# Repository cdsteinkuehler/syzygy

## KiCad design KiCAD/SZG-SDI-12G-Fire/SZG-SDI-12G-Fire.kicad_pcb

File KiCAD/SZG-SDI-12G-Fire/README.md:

# SYZYGY 12G SDI Pod

This directory contains KiCad 7 design files for a SYZYGY 12G SDI Pod
intended to be used with the BeagleV-Fire SYZYGY connector and 12G
capable transceivers.

Near as I can tell, the SYZYGY Template PCB designs from Opal Kelly are
licensed under the SYZYGY Specification License Agreement (or at least
I was unable to find any other license information specifically related
to the PCB templates).  My changes to the template design are licensed
under the CERN CERN-OHL-P v2 (permissive) license to the extent this
does not conflict with the SYZYGY license agreement.

NOTE: Power rail separation for the SDI chips matches the Semtech Intel
FPGA Arria 10 Reference Design Daughter Card implementation vs. the
application circuit notes provided in the data sheets.

## License Info

Copyright Charles Steinkuehler 2024.

This source describes Open Hardware and is licensed under the CERN-OHL-P
v2

You may redistribute and modify this documentation and make products
using it under the terms of the CERN-OHL-P v2 (https:/cern.ch/cern-ohl).
This documentation is distributed WITHOUT ANY EXPRESS OR IMPLIED
WARRANTY, INCLUDING OF MERCHANTABILITY, SATISFACTORY QUALITY
AND FITNESS FOR A PARTICULAR PURPOSE. Please see the CERN-OHL-P v2
for applicable conditions

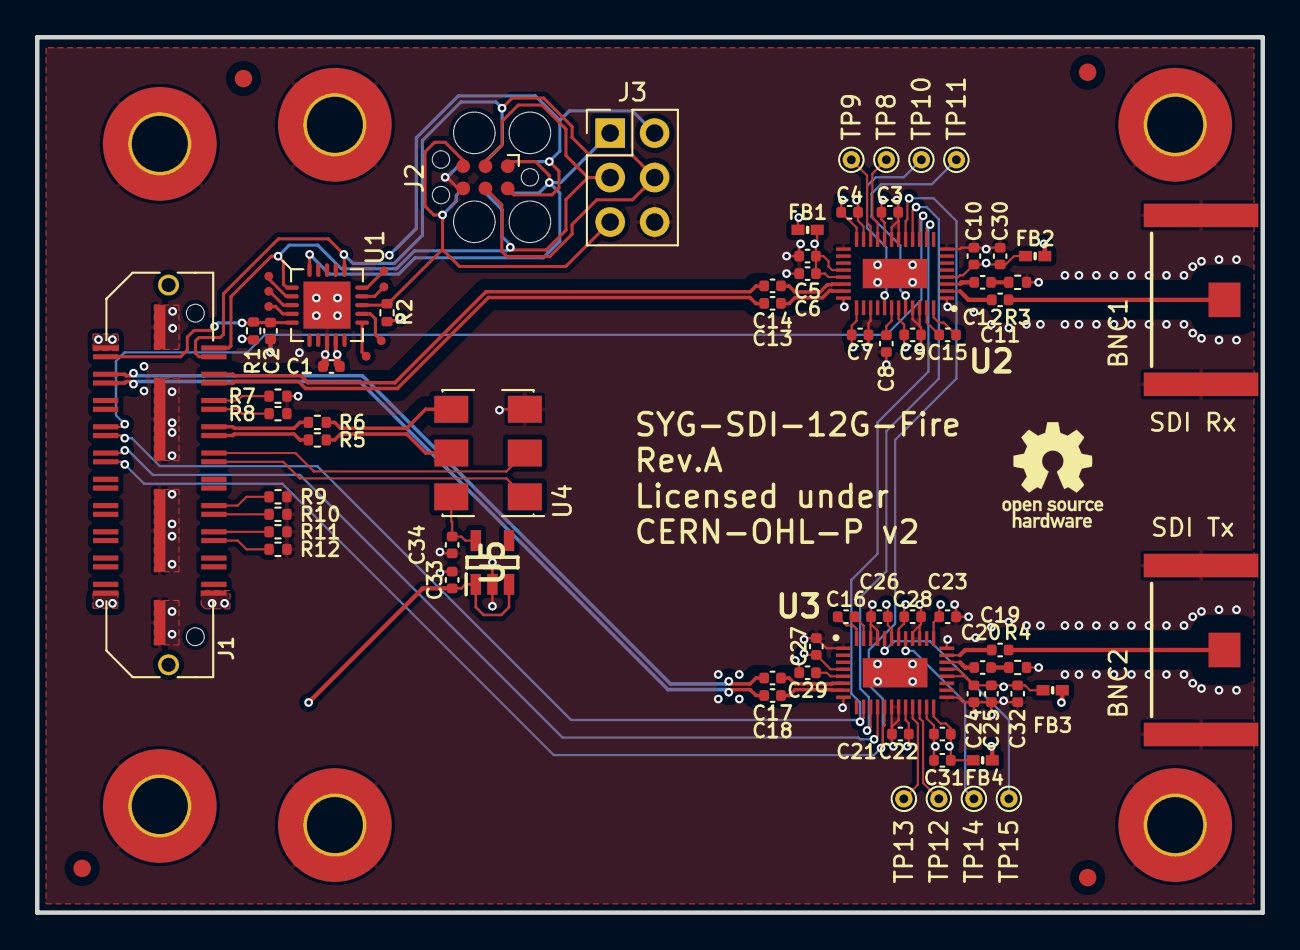
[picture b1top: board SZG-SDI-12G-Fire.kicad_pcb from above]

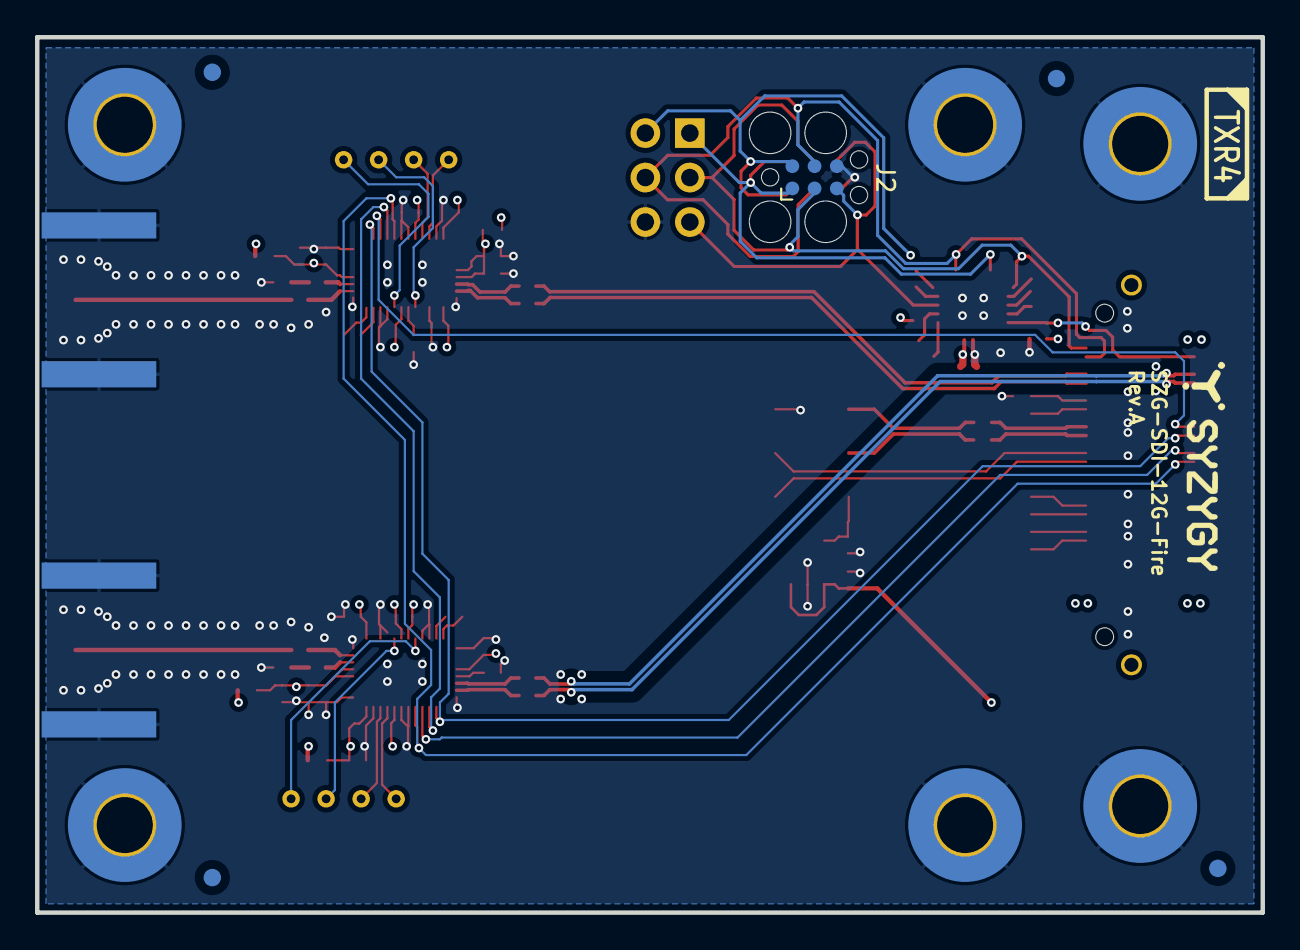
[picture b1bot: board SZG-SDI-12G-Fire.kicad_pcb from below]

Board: 4 copper layers, 70.0 x 50.0 mm, 91 parts (13 on the bottom side), 68 nets.

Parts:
BNC1, BNC2: BNC; BNC7T-J-P-XX-ST-EM1D
C1, C3, C4, C5, C6, C7, C21, C22, C23, C24, C25, C29: 0.1uF; C_0402_1005Metric
C2: 0.1uF DNP; C_0402_1005Metric
C8, C9, C26, C28, C30, C31, C32: 10uF; C_0402_1005Metric
C10, C27, C33, C34: 1.0uF; C_0402_1005Metric
C11, C12, C13, C14, C17, C18, C19, C20: 4.7uF; C_0402_1005Metric
C15, C16: 470nF; C_0402_1005Metric
FB1, FB2, FB3, FB4: Ferrite; BEADC1005X55N
FID1, FID2, FID3, FID4, FID5, FID6, FID7, FID8: Fiducial; Fiducial_1mm_Mask2mm
H1, H2, H3, H4, H5, H6: MountingHole_Pad; MountingHole_3.2mm_M3_6.5mm_Pad_TopBottom
J1: SYZYGY_TXR-4; QTH-020-01-F-D-DP-A
J2: Conn_01x06; Tag-Connect_TC2030-IDC-FP_2x03_P1.27mm_Vertical
J3: Conn_02x03_Odd_Even; PinHeader_2x03_P2.54mm_Vertical
LOGO1: SYZYGY_STD_Logo; SYZYGY_TXR4_Logo
LOGO2: LOGO; SYZYGY_Logo
R1, R2: 10K; R_0402_1005Metric
R3: 2.0R; R_0402_1005Metric
R4: 75R; R_0402_1005Metric
R5, R6, R7, R8, R9, R10, R11, R12: 0R; R_0402_1005Metric
TP1, TP2, TP3, TP4, TP5, TP6, TP7: TestPoint; TestPoint-20mil
TP8, TP9, TP10, TP11, TP12, TP13, TP14, TP15: TestPoint; TestPoint_THTPad_D1.0mm_Drill0.5mm
U1: ATtiny44A-MU; QFN-24-4x4mm
U2: GS12241-INE3; QFN40P600X400X100-41N-D
U3: GS12281-INTE3; QFN40P600X400X100-41N-D
U4: 513FCA000270AAG; Si513-A
U5: LP5907MFX-2.5/NOPB; SOT95P280X145-5N

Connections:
+3V3: C1.1, C33.1, FB3.1, J1.40 (+3.3V), J2.2, J3.2, R1.1, R2.1, U1.9 (VCC), U5.1 (IN), U5.3 (EN)
/+2.5V: C34.1, U4.6 (VDD), U5.5 (OUT)
/AVR/MCU_MISO: J2.1, J3.1, U1.20 (PA5)
/AVR/MCU_RESET_B: J2.5, J3.5, R2.2, U1.13 (~RESET/PB3)
/CLKN: R5.1, U4.5 (CLK-)
/CLKP: R6.1, U4.4 (CLK+)
/CLK_FS: J1.17 (S2), U4.2 (FS)
/CLK_OE: J1.19 (S4), U4.1 (OE)
/CS_n: J1.16 (S1), U2.10 (~CS), U3.10 (~CS)
/MCU_SCL_USCK: J1.1 (SCL), J2.3, J3.3, U1.1 (PA4)
/MCU_SDA_MOSI: J1.3 (SDA), J2.4, J3.4, U1.16 (PA6)
/REFCLKN: J1.15 (REFCLKn), R5.2
/REFCLKP: J1.13 (REFCLKp), R6.2
/RX0N: C13.2, J1.7 (RX0n)
/RX0P: C14.2, J1.5 (RX0p)
/RX1N: J1.11 (RX1n), R8.1
/RX1P: J1.9 (RX1p), R7.1
/RX2N: J1.31 (RX2n), R12.1
/RX2P: J1.29 (RX2p), R11.1
/RX3N: J1.27 (RX3n), R10.1
/RX3P: J1.25 (RX3p), R9.1
/R_GA: C2.1, J1.4 (R_GA), R1.2, U1.5 (AREF/PA0)
/SCLK: J1.20 (S5), U2.13 (SCLK), U3.13 (SCLK)
/SDI/GPIO0: TP9.1, U2.18 (GPIO_1)
/SDI/GPIO1: TP8.1, U2.17 (GPIO_0)
/SDI/GPIO2: TP10.1, U2.33 (GPIO_2)
/SDI/GPIO3: TP11.1, U2.36 (GPIO_3)
/SDI/GPIO4: TP13.1, U3.17 (GPIO0)
/SDI/GPIO5: TP12.1, U3.18 (GPIO1)
/SDI/GPIO6: TP14.1, U3.33 (GPIO2)
/SDI/GPIO7: TP15.1, U3.36 (GPIO3)
/SDI/RxCN: C14.1, U2.26 (~DDO0)
/SDI/RxCP: C13.1, U2.27 (DDO0)
/SDI/SDIX: U2.12 (SDOUT), U3.11 (SDIN)
/SDI/SDI_N: C12.2, U2.3 (SDI_TERM)
/SDI/SDI_P: C11.2, U2.2 (SDI)
/SDI/SDI_X: BNC1.1 (In), C11.1
/SDI/SDO_N: C20.1, U3.26 (~SDO0)
/SDI/SDO_P: C19.1, U3.27 (SDO0)
/SDI/SDO_X: BNC2.1 (In), C19.2
/SDI/TERMO: C29.1, U3.5 (TERM)
/SDI/TxCN: C18.2, U3.7 (~DDI)
/SDI/TxCP: C17.2, U3.6 (DDI)
/SDI/VCCO_I: C5.1, C6.1, FB1.2, U2.24 (VCCO_1), U2.25 (VCCO_0)
/SDI/VCCO_O: C24.1, C25.1, C32.1, FB3.2, U3.24 (VCCO_1), U3.25 (VCCO_0)
/SDI/VCC_I: C4.1, C7.1, C9.1, C10.1, C30.1, FB2.2, U2.4 (VCC_SDI), U2.20 (VCCO1P8_1), U2.29 (VCCO1P8_0), U2.35 (VCC_CORE)
/SDI/VCC_O: C22.1, C23.1, C26.1, C27.1, C31.1, FB4.2, U3.4 (VCC_DDI), U3.20 (VCCO1P8_1), U3.29 (VCCO1P8_0), U3.35 (VCC_CORE)
/SDI/VCO_I: C8.1, U2.34 (VCO_FILT)
/SDI/VCO_O: C28.1, U3.34 (VCO_FILT)
/SDIN: J1.14 (S0), U2.11 (SDIN)
/SDOUT: J1.18 (S3), U3.12 (SDOUT)
/TX0N: C18.1, J1.8 (TX0n)
/TX0P: C17.1, J1.6 (TX0p)
/VIO: C3.1, C21.1, FB1.1, FB2.1, FB4.1, J1.39 (VIO), U2.16 (VDD), U3.16 (VDD)
GND: BNC1.2 (Ext), BNC2.2 (Ext), C1.2, C2.2, C3.2, C4.2, C5.2, C6.2, C7.2, C8.2, C9.2, C10.2, C21.2, C22.2, C23.2, C24.2, C25.2, C26.2, C27.2, C28.2, C29.2, C30.2, C31.2, C32.2, C33.2, C34.2, H1.1, H2.1, H3.1, H4.1, H5.1, H6.1, J1.0 (GND), J2.6, J3.6, R3.1, R4.2, R7.2, R8.2, R9.2, R10.2, R11.2, R12.2, U1.8 (GND), U1.21 (GND), U2.1 (VEE_SDI_1), U2.8 (VEE_SDI_2), U2.14 (VSS_1), U2.15 (VSS_2), U2.19 (VEE_CORE_1), U2.21 (VEEO_1), U2.28 (VEEO_2), U2.31 (VEE_CORE_2), U2.37 (VEE_CORE_3), U2.38 (VEE_CORE_4), U2.41 (TAB), U3.1 (VEE_DDI_1), U3.8 (VEE_DDI_2), U3.14 (VSS_1), U3.15 (VSS_2), U3.19 (VEE_CORE_1), U3.21 (VEEO_1), U3.28 (VEEO_2), U3.31 (VEE_CORE_2), U3.32 (REF_CLK), U3.37 (VEE_CORE_3), U3.38 (VEE_CORE_4), U3.41 (EP), U4.3 (GND), U5.2 (GND)
unnamed: C12.1, R3.2
unnamed: C20.2, R4.1
unnamed: TP1.1, U1.4 (PA1)
unnamed: TP2.1, U1.3 (PA2)
unnamed: TP3.1, U1.2 (PA3)
unnamed: TP4.1, U1.15 (PA7)
unnamed: TP7.1, U1.14 (PB2)
unnamed: TP5.1, U1.11 (XTAL1/PB0)
unnamed: TP6.1, U1.12 (XTAL2/PB1)
unnamed: C15.2, U2.39 (LF+)
unnamed: C15.1, U2.40 (LF-)
unnamed: C16.2, U3.39 (LF+)
unnamed: C16.1, U3.40 (LF-)

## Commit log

2023-12-30 Initial 12G SDI Design
    Schematic should be complete
    PCB has BeagleV-Fire outline imported for reference, but needs to be
    updated to match schematic.
2024-01-01 Initial version: Rev.A
    Minor schematic tweaks for routing and to address SDI Rx/Tx power rails
    PCB fully placed and routed
    Added README/CHANGES files
    Added CERN-OHL-P v2 license file
2024-01-15 Update with part numbers
    Add manufacturer part numbers as ordered from DigiKey
    Add stitching vias on PCB for SDI 75 ohm striplines
